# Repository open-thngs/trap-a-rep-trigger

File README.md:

# Openthing 2 - RepTrap 

The RepTrap is a "motion detector" and camera trigger designed to detect small and/or cold-blooded animals such as frogs, lizards, birds, and other wildlife. It doesn't detect motion directly but instead identifies changes in height within the range of its four Time-of-Flight (ToF) sensors. Any height change within this range triggers a connected camera's shutter.

## BLE 

The device and software is Bluetooth ready but it is currently missing an App. Here are commands which can be send to configure and change the device:

- Bluetooth Service [`0x7017`]
    - **Status** Characteristic [`0x701C`]
      **Description**: Refelcts the current device status as a string
      **Values**: `running` `calibrating`
    - **Command** Characteristic [`0x7018`]
      **Description**: Accepts specific device commands
      **Values:**
      - `stop`: Stops the BLE Service on the device
      - `calibrate`: Triggers a re-calibration of the device
      - `xtalk`: Triggers an cross-talk and offset calibration of the device (only needed for manufacturing, should not be used)
      - `trigger`: Triggers the camera shutter and focus signal
    - **Config** Characteristic [`701D`]
      **Description**: Using this characteristic you can configure the device (**experimental**). You can send a 3 Byte payload consisting of the type (first byte) and tzhe data(second and third byte). Example `[0xA0, 0x00, 0x00]` Type 0xA0 Signal Threashold with value 0
      **Values**:
        - `0xA0` - Signal Threshold
        - `0xA1` - Sigma Threshold
        - `0xA2` - Time to Measure
        - `0xA3` - Measure Interval

**Note:** The config characteristic is experimental. The limits of the values might not be checked or some value combination might lead to an unresponsive sensor. A re-flash of the firmware might be needed to fix the device. You can read the datasheet of the ToF Sensor to get the details of this values.

**Note:** If you want to power the device permanently via USB-C the BLE Service will be started once you boot the device with USB-C connected. You can send teh command to stop the BLE Service to save energy.

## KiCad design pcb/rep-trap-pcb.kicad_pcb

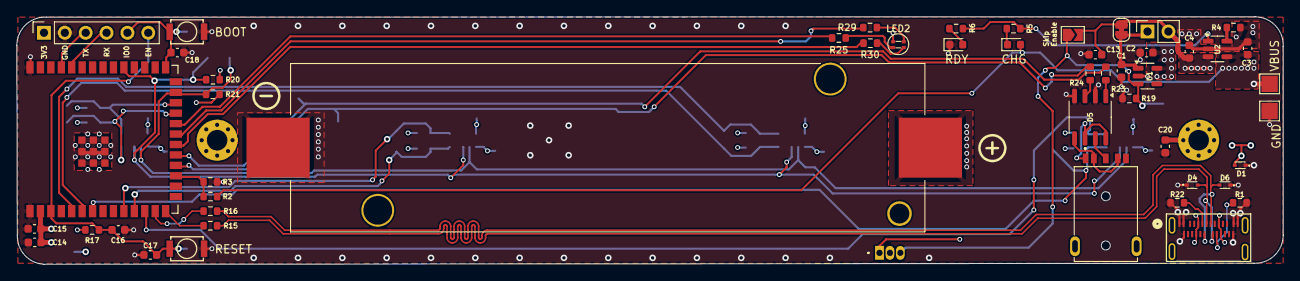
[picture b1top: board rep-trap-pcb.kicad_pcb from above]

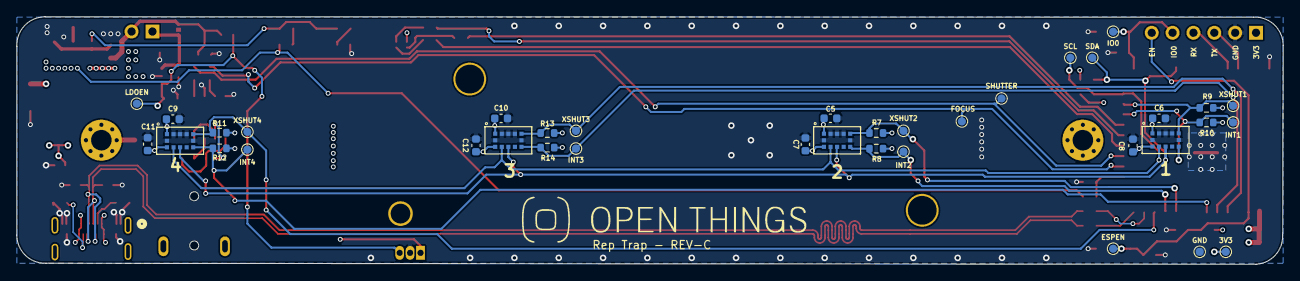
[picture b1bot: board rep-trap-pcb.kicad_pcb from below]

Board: 4 copper layers, 154.2 x 30.1 mm, 91 parts (38 on the bottom side), 45 nets.

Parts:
BT1: BH-18650-B1BA002; 1042P
C1, C2, C16: 1µF; C_0603_1608Metric
C3, C4, C14: 10µF; C_0603_1608Metric
C5, C6, C9, C10: 4.7µF; C_0603_1608Metric
C7, C8, C11, C12, C13, C15, C20: 0.1µF; C_0603_1608Metric
C17, C18: 0.1µF/DNP; C_0603_1608Metric
D1, D4, D6: LESD5D5.0CT1G; LESD5D50CT1G
D2: LED_RED; LED_0603_1608Metric
D3: LED_GREEN; LED_0603_1608Metric
D5: ILD213T; SO-8_3.9x4.9mm_P1.27mm
G1: LOGO
H1, H2: MountingHole_Pad; MountingHole_2.5mm_Pad_Via
IC1: DRV5032FBLPG; DRV5032DULPGM
J3: PJ-3254A-SMT; CUI_SJ-3541AS-SMT-TR-67
J4: VBUS; TestPoint_Pad_2.0x2.0mm
J5: Conn_01x02_Pin; PinSocket_1x02_P2.54mm_Vertical
J7: GND; TestPoint_Pad_2.0x2.0mm
J8: 124018612112A; CONN_124018612112A_AMP
J9: DNP; PinSocket_1x06_P2.54mm_Vertical
JP1: SolderJumper_2_Open; SolderJumper-2_P1.3mm_Open_TrianglePad1.0x1.5mm
JP2: Jumper_2_Bridged; SolderJumper-2_P1.3mm_Bridged_RoundedPad1.0x1.5mm
LED2: APHF1608LSEEQBDZGKC
R1, R22: 5k1; R_0603_1608Metric
R2: 4.7k; R_0603_1608Metric
R3, R7, R8, R9, R10, R11, R12, R13, R14, R17: 10k; R_0603_1608Metric
R4: 2k; R_0603_1608Metric
R5, R6: 1k; R_0603_1608Metric
R15, R16: 0R; R_0603_1608Metric
R19: 10k/DNP; R_0603_1608Metric
R20, R21, R29: 2.2k; R_0603_1608Metric
R23, R24: 47R; R_0603_1608Metric
R25: 1k2; R_0603_1608Metric
R30: 390R; R_0603_1608Metric
SW1, SW2: SKRKAEE020
TP1: TB_SDA; TestPoint_Pad_D1.0mm
TP2: TP_SCL; TestPoint_Pad_D1.0mm
TP3, TP17: TP_3V3; TestPoint_Pad_D1.0mm
TP4: TP_XSHUT_1; TestPoint_Pad_D1.0mm
TP5: TP_INT_1; TestPoint_Pad_D1.0mm
TP6: TP_XSHUT_2; TestPoint_Pad_D1.0mm
TP7: TP_INT_2; TestPoint_Pad_D1.0mm
TP8: TP_XSHUT_4; TestPoint_Pad_D1.0mm
TP9: TP_INT_4; TestPoint_Pad_D1.0mm
TP10: TP_XSHUT_3; TestPoint_Pad_D1.0mm
TP11: TP_INT_3; TestPoint_Pad_D1.0mm
TP12: TP_EN_ESP; TestPoint_Pad_D1.0mm
TP13: TP_GPIO0; TestPoint_Pad_D1.0mm
TP14: TP_LDO_EN; TestPoint_Pad_D1.0mm
TP15: TP_SHUTTER; TestPoint_Pad_D1.0mm
TP16: TP_FOCUS; TestPoint_Pad_D1.0mm
U1: AP2112K-3.3; SOT-23-5
U2: MCP73831/OT; SOT-23-5
U3, U4, U5, U6: VL53L4CDV0DH/1; LGA12_STM
U7: ESP32-S3-WROOM-1

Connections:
+3.3V: C2.1, C5.1, C6.1, C7.1, C8.1, C9.1, C10.1, C11.1, C12.1, C14.1, C15.1, J9.1, LED2.1 (A), R7.2, R8.2, R9.2, R10.2, R11.2, R12.2, R13.2, R14.2, R17.2, R20.2, R21.2, TP3.1, U1.5 (VOUT), U3.1 (AVDDVCSEL), U3.11 (AVDD), U4.1 (AVDDVCSEL), U4.11 (AVDD), U5.1 (AVDDVCSEL), U5.11 (AVDD), U6.1 (AVDDVCSEL), U6.11 (AVDD), U7.2 (3V3)
+BATT: BT1.1 (+), C4.1, C13.1, IC1.1 (VCC), J5.2, JP1.2 (B), JP2.2 (B), U2.3 (V_{BAT})
/main/AUTOFOCUS: R24.1, TP16.1, U7.18 (GPIO10/TOUCH10/ADC1_CH9/FSPICS0/FSPIIO4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)
/main/ENABLE: IC1.3 (OUT2), JP1.1 (A), R19.2, TP14.1, U1.3 (EN)
/main/END: D5.6 (COLLECTOR_1), D5.8 (COLLECTOR_2), J3.1
/main/MCU/EN: C16.1, C17.1, J9.6, R17.1, SW2.2, TP12.1, U7.3 (EN)
/main/MCU/GPIO_0: C18.1, J9.5, SW1.2, TP13.1, U7.27 (GPIO0/BOOT)
/main/MCU/LED_B: R30.1, U7.20 (GPIO12/TOUCH12/ADC2_CH1/FSPICLK/FSPIIO6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)
/main/MCU/LED_G: R29.1, U7.21 (GPIO13/TOUCH13/ADC2_CH2/FSPIQ/FSPIIO7/S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)
/main/MCU/LED_R: R25.2, U7.22 (GPIO14/TOUCH14/ADC2_CH3/FSPIWP/FSPIDQS/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)
/main/MCU/SCL: R21.1, TP2.1, U3.10 (SCL), U4.10 (SCL), U5.10 (SCL), U6.10 (SCL), U7.25 (GPIO48/SPICLK_N/SUBSPICLK_N_DIFF)
/main/MCU/SDA: R20.1, TP1.1, U3.9 (SDA), U4.9 (SDA), U5.9 (SDA), U6.9 (SDA), U7.31 (GPIO38/FSPIWP/SUBSPIWP)
/main/MCU/U0RXD: J9.4, U7.36 (U0RXD/GPIO44/CLK_OUT2)
/main/MCU/U0TXD: J9.3, U7.37 (U0TXD/GPIO43/CLK_OUT1)
/main/MCU/USB_DM: R16.1, U7.13 (GPIO19/U1RTS/ADC2_CH8/CLK_OUT2/USB_D-)
/main/MCU/USB_DP: R15.1, U7.14 (GPIO20/U1CTS/ADC2_CH9/CLK_OUT1/USB_D+)
/main/MCU/~INT_VL53_1: R10.1, TP5.1, U4.7 (GPIO1), U7.23 (GPIO21)
/main/MCU/~INT_VL53_2: R8.1, TP7.1, U3.7 (GPIO1), U7.11 (GPIO18/U1RXD/ADC2_CH7/CLK_OUT3)
/main/MCU/~INT_VL53_3: R14.1, TP11.1, U6.7 (GPIO1), U7.6 (GPIO6/TOUCH6/ADC1_CH5)
/main/MCU/~INT_VL53_4: R12.1, TP9.1, U5.7 (GPIO1), U7.7 (GPIO7/TOUCH7/ADC1_CH6)
/main/MCU/~XSHUT_VL53_1: R9.1, TP4.1, U4.5 (XSHUT), U7.24 (GPIO47/SPICLK_P/SUBSPICLK_P_DIFF)
/main/MCU/~XSHUT_VL53_2: R7.1, TP6.1, U3.5 (XSHUT), U7.10 (GPIO17/U1TXD/ADC2_CH6)
/main/MCU/~XSHUT_VL53_3: R13.1, TP10.1, U6.5 (XSHUT), U7.5 (GPIO5/TOUCH5/ADC1_CH4)
/main/MCU/~XSHUT_VL53_4: R11.1, TP8.1, U5.5 (XSHUT), U7.12 (GPIO8/TOUCH8/ADC1_CH7/SUBSPICS1)
/main/PSU and charging/STAT: R5.1, R6.1, U2.1 (STAT)
/main/PSU and charging/VIN: C1.1, J5.1, JP2.1 (A), U1.1 (VIN)
/main/RING: D5.7 (EMITTER_2), J3.3
/main/SHUTTER: R23.1, TP15.1, U7.19 (GPIO11/TOUCH11/ADC2_CH0/FSPID/FSPIIO5/S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)
/main/TIP: D5.5 (EMITTER_1), J3.2, J3.5
/main/USB_D+: D4.2 (A2), J8.A6 (D1+), J8.B6 (D2+), R15.2
/main/USB_D-: D6.2 (A2), J8.A7 (D1-), J8.B7 (D2-), R16.2
/main/VBUS_DETECT: R2.2, R3.1, U7.17 (GPIO9/TOUCH9/ADC1_CH8/FSPIHD/SUBSPIHD)
GND: BT1.2 (-), C1.2, C2.2, C3.2, C4.2, C5.2, C6.2, C7.2, C8.2, C9.2, C10.2, C11.2, C12.2, C13.2, C14.2, C15.2, C16.2, C17.2, C18.2, C20.2, D1.1 (A1), D3.1 (K), D4.1 (A1), D5.2 (CATHODE_1), D5.4 (CATHODE_2), D6.1 (A1), IC1.2 (GND), J7.1, J8.25 (GND), J8.26 (GND), J8.A1 (GND_A), J8.A12 (GND_A), J8.B1 (GND_B), J8.B12 (GND_B), J9.2, R1.1, R3.2, R4.2, R19.1, R22.1, SW1.1, SW2.1, TP17.1, U1.2 (GND), U2.2 (V_{SS}), U3.2 (AVSSVCSEL), U3.3 (GND), U3.4 (GN2), U3.6 (GND3), U3.12 (GND4), U4.2 (AVSSVCSEL), U4.3 (GND), U4.4 (GN2), U4.6 (GND3), U4.12 (GND4), U5.2 (AVSSVCSEL), U5.3 (GND), U5.4 (GN2), U5.6 (GND3), U5.12 (GND4), U6.2 (AVSSVCSEL), U6.3 (GND), U6.4 (GN2), U6.6 (GND3), U6.12 (GND4), U7.1 (GND), U7.40 (GND), U7.41 (GND)
unnamed: C20.1, H1.1
unnamed: D2.1 (K), R5.2
unnamed: D3.2 (A), R6.2
unnamed: D5.1 (ANODE_1), R23.2
unnamed: D5.3 (ANODE_2), R24.2
unnamed: J8.A5 (CC1), R22.2
unnamed: J8.B5 (CC2), R1.2
unnamed: LED2.3 (B), R30.2
unnamed: LED2.4 (G), R29.2
unnamed: LED2.2 (R), R25.1
unnamed: R4.1, U2.5 (PROG)
VBUS: C3.1, D1.2 (A2), D2.2 (A), J4.1, J8.A4 (VBUS_A), J8.A9 (VBUS_A), J8.B4 (VBUS_B), J8.B9 (VBUS_B), R2.1, U2.4 (V_{DD})

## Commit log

2023-07-01 Added initial PCB project
2023-07-01 Added prototyping code for validating multiple sensor usage
2023-07-05 Added first components and size check
2023-07-13 Added pcb design for first prototype
2023-07-13 Added Logo + Revision + generated Bom
2023-07-14 Refactored details component namings + bom excludings
2023-07-14 Moved via out of the pad
2023-07-14 Applied the vias of the RP2040
2023-07-26 Removed debounce IC and replaced with default on off switch
2023-08-02 Applied ERC issue changes + DRC issues fix
2023-08-02 Added MIT License
2023-08-07 Add kibot config file
2023-08-07 Added more options to the kibot config for bom generation, 3d file etc.
2023-08-07 Added missing list to gerber generation
2023-08-07 set z rotation to 0
2023-08-08 Added basic kibot config
2023-08-16 Added notes and ToDos to be worked on for REV.02
2023-08-16 Changed code to calibrate the sensor on boot and trigger only once after detection
2023-08-25 Currentfirmware state with temperature update and calibration
2023-08-25 Added housing 3D file done with sketcher
2023-09-03 removed gitlab action
2023-09-03 Add pcb-draw to KiBot output
2023-09-03 Changed KiBot action names differently
2023-09-03 Added style for printed PCB images
2023-09-03 Removed style again for now
2023-09-05 Added In1.Cu and In2.Cu to the gerber export
2023-09-07 Current Firmware state incl. manufacturing calibration, height calibration threashold and sleep mode (bad)
2023-09-27 Add board setup for micropython
2023-09-27 Added LED blinking once calibration is done
2023-09-27 Changed board id back to be pico
2023-09-28 Only run firmware action on tag or push to src folder
2023-09-28 Run kibot action only on changes in pcb folder or tags
2023-10-03 Disable sleep
2023-10-03 lowered measurment timings to detect objects faster
2023-10-03 Decreased signal threashold
2023-10-03 Re-enable sleep again
2024-01-07 refactored components and layout
2024-02-05 re-organise components + added housing data
2024-02-05 Added upload script to upload all micropython files + changed values to trigger much faster (more power consumption)
2024-02-07 Replaced RP2040 with ESP32 + Schematics + Layouting
2024-02-07 Added workflow dispatch to kibot.yml
2024-02-09 Changed Battery silk to plus and minus + added 18650 battery STEP file to the battery holder
2024-02-10 Connected PCB GND with enclosure mounting screws
2024-02-12 Added dimension scales
2024-02-12 Renamed tracks to fix ERC warnings
2024-02-12 Modified components to fix ERC issues
2024-02-12 Add lck file to be ignored
2024-02-12 Add lck file to be ignored and not tracked
2024-02-12 Fix thermal relieve gap
2024-02-12 Fix DRC issue TH vs. SMD
2024-02-12 Fixed wrong ESP32-S3 footprint
2024-02-12 Added missing 3D Step file for ESP32-S3
2024-02-12 Changed 3d rendering view
2024-02-12 Try to ignore DRC issues
2024-02-12 Fixed ESP32-S3 footprint and symbol issues
2024-02-12 Removed DNP components from BOM
2024-02-16 Removed diode from VBUS to 5V+ and removed 5V+ because it is not needed
2024-02-16 Removed capacitor from one of the mountingholes
2024-02-19 Changed net names to match functionallity of active low
2024-03-07 Moved magnet switch to the other side
2024-03-07 Added new housing + magent switch
2024-03-07 Updated footprints try to fix DRC
2024-03-15 Fixed usage of strapping pins
2024-03-18 Swapped 100-Ohms with 47-Ohms for the optocoupler
2024-03-18 Added toit test code
2024-03-18 Mark oull-down resistor for EN pin as DNP
2024-03-18 Updated PCB with changed values
2024-03-20 Added test for usb-c detect
2024-03-20 Added Enclosure changes and removed old enclosure data
2024-04-02 Added print status function to the driver t oget a readable status
2024-04-02 Applied changes for the new hardware revision + rgbled + dedicated calibrator function
2024-04-02 Renamed upload to sync and added start of putty to the end
2024-04-03 Started implementing toit code
2024-04-05 Refactored toit implementation
    ISSUE: measurment of the sensors return 0 most of the time
2024-04-05 This toit code works now incl. calibration
2024-04-05 Refactored python code to use percentage instead of std-deviation
2024-04-08 Added BLE service to trigger the camera from remote and re-calibrate the sensor remotely
2024-04-08 Added stl for the glas and step file for the latch
2024-04-08 Add package folder to git ignore
2024-04-08 Added changes to pcb + added production files from latest generation
2024-04-09 Added sensor manager and refactored code to fix issues the gpio containers
2024-04-12 Changed interrupt polarity to match HIGH instead of LOW + add correct way to finish BLE service
    Note: interrupt seems only to work with sensor 4
2024-04-12 Reversed the interrupt from high active back to low active
2024-04-14 Refactored gpio input constructor usage in example
2024-04-14 Moved hardcoded RGB LED gpio declaration into the rgb-led class
2024-04-14 Refactored calibrator to use sensor-manager
2024-04-14 Refactored code to be launched with jaguar instead of asrtemis to decrease trigger time
    trigger time: 220ms instead 600
    BLE container boots after boot whan ucb is detected
    BLE container will stop if usb is disconnected or stopped via BLE
2024-04-14 Add artemis package
2024-04-14 Added development app for BLE App
2024-04-15 Refactored disable vl53 device
2024-04-15 Added BLE device state + fixed crashes + removed unused code
2024-04-17 Added license files for housing files
2024-04-17 Added calibration holder 3d print file
2024-04-17 Added 3ddescription image license information
2024-04-22 Refactored code and save current state of development
2024-04-22 Applied changes for full firmware build without jaguar
2024-04-22 Create none working main.yml to generate firmware for toit
2024-04-22 Add example container to send firmware via ble
2024-04-22 Changed workflow to generate toit firmware
2024-04-22 Change gitignore file to ignore .packages folder
2024-04-22 Add shell script to compile and deploy firmware localy
2024-04-22 Fix firmware.yaml run only on tag and not on push
2024-04-22 Modified toit yaml to use environment variable to reference the toit version
2024-04-22 Fix call to toit.compile with a dot
2024-04-22 Updated used toit libraries
2024-04-22 install toit libraries before compiling
2024-04-22 Applied changes to app.py micropython code
2024-04-23 Fix and clean toit firmware generation github action
2024-04-23 Removed unused MIT license
2024-04-23 Only run toit firmware generation on release created
2024-04-23 Add generated toit firmware file to the release assets
2024-04-23 Fix upload issue
2024-04-23 Try to fix release upload assets
2024-04-23 try uploading artifacts again using github action for release upload
2024-04-23 Run toit.yml on tag (not on release) because it does create a release now
2024-04-23 Change uploaded asset from zip to be bin
2024-04-23 Add missing license for build script
2024-04-23 Add readme for toit project
2024-04-23 Add changed pcb files
2024-04-23 Run kibot action only on tags with pcb*
2024-04-28 All changes since last working version
2024-04-28 Finally seem to fixed the sensor issues
2024-04-28 Fix pin extract
2024-04-29 Set xshunt off on initialisation
2024-04-30 Add wait-for-boot before changing i2c address
2024-04-30 correctly configure xshunt pins
2024-05-01 Disabled sensor 2 and added original low power code t oset inter-measurment-ms and timing-busget
2024-05-01 Turning off sensor 2 entirly
2024-05-07 Fix decoupling cap swap + refactored and cleaned the layout a bit
2024-05-07 Moved vias further away from the sensors + added silk on bottom side for debug connector
2024-05-07 Removed unnecessary 10ms sleep after each i2c write
2024-05-07 Set I2C ADDR for the VL53L4CD Sensor further appart due to address collisions
2024-05-07 Set I2C frequency to 300.000 insteat of 400k to avoid wierd spikes on SDA + removed 1s sleep after each sensor init
2024-05-07 Add unwind to make stacktrace show up in log
2024-05-07 Removed handling of 0mm until we found out why this happens
2024-05-07 Added Testpoints on bottom side
2024-05-07 Updated footprint for DRC errors
2024-05-08 Try to fix warnings by actually using the exclusions from KiCad with KiBot
2024-05-08 Ignore Warning 58 (Footprint does not match copy in library)
2024-05-08 Update to use KiCad8
2024-05-08 micropython: changed get-distance to get-result and beautify prints
2024-05-13 Add 3ms sleep after i2c write to fix the issue with the sensors
2024-05-13 Reduced trigger time by 60ms+ by not spawning and pass rgb-led
2024-05-17 Refactored code +fixed USB-C unplug device reset + fix blink after calibration finished
2024-05-17 Getting back to old values incl. 400k i2c speed
2024-05-27 Added signal-threshold, sigma-threshold, time-to-measure and interval for measurments as configurables to BLE
2024-05-28 Fixed trigger in BLE mode to only run once and ignore multiple calls
2024-05-28 Fix calibration of xtalk (still seems to breack the sensor)
2024-05-28 Refactored task irq cancelation
2024-05-28 Fixed to only run BLE if the device was hard reset and USB-C is connected
2024-06-01 Add version file to release artefacts
2024-06-01 try to create a version file
2024-06-01 removed version file for now
2024-09-30 Add gitlab path to OTS updates to BLE OTA example app
2024-09-30 Add more test apps
2024-11-06 updated housing files
2024-11-06 PCB update
2024-11-06 added latest firmware envelope
2024-11-06 fabrication tool options update
2024-11-06 Added second version for micropython testing
2024-11-21 Fix images links
2024-11-21 Still trying to fix images in the readme
2024-11-21 Add missing License
2024-11-21 Update readme with BLE informations
